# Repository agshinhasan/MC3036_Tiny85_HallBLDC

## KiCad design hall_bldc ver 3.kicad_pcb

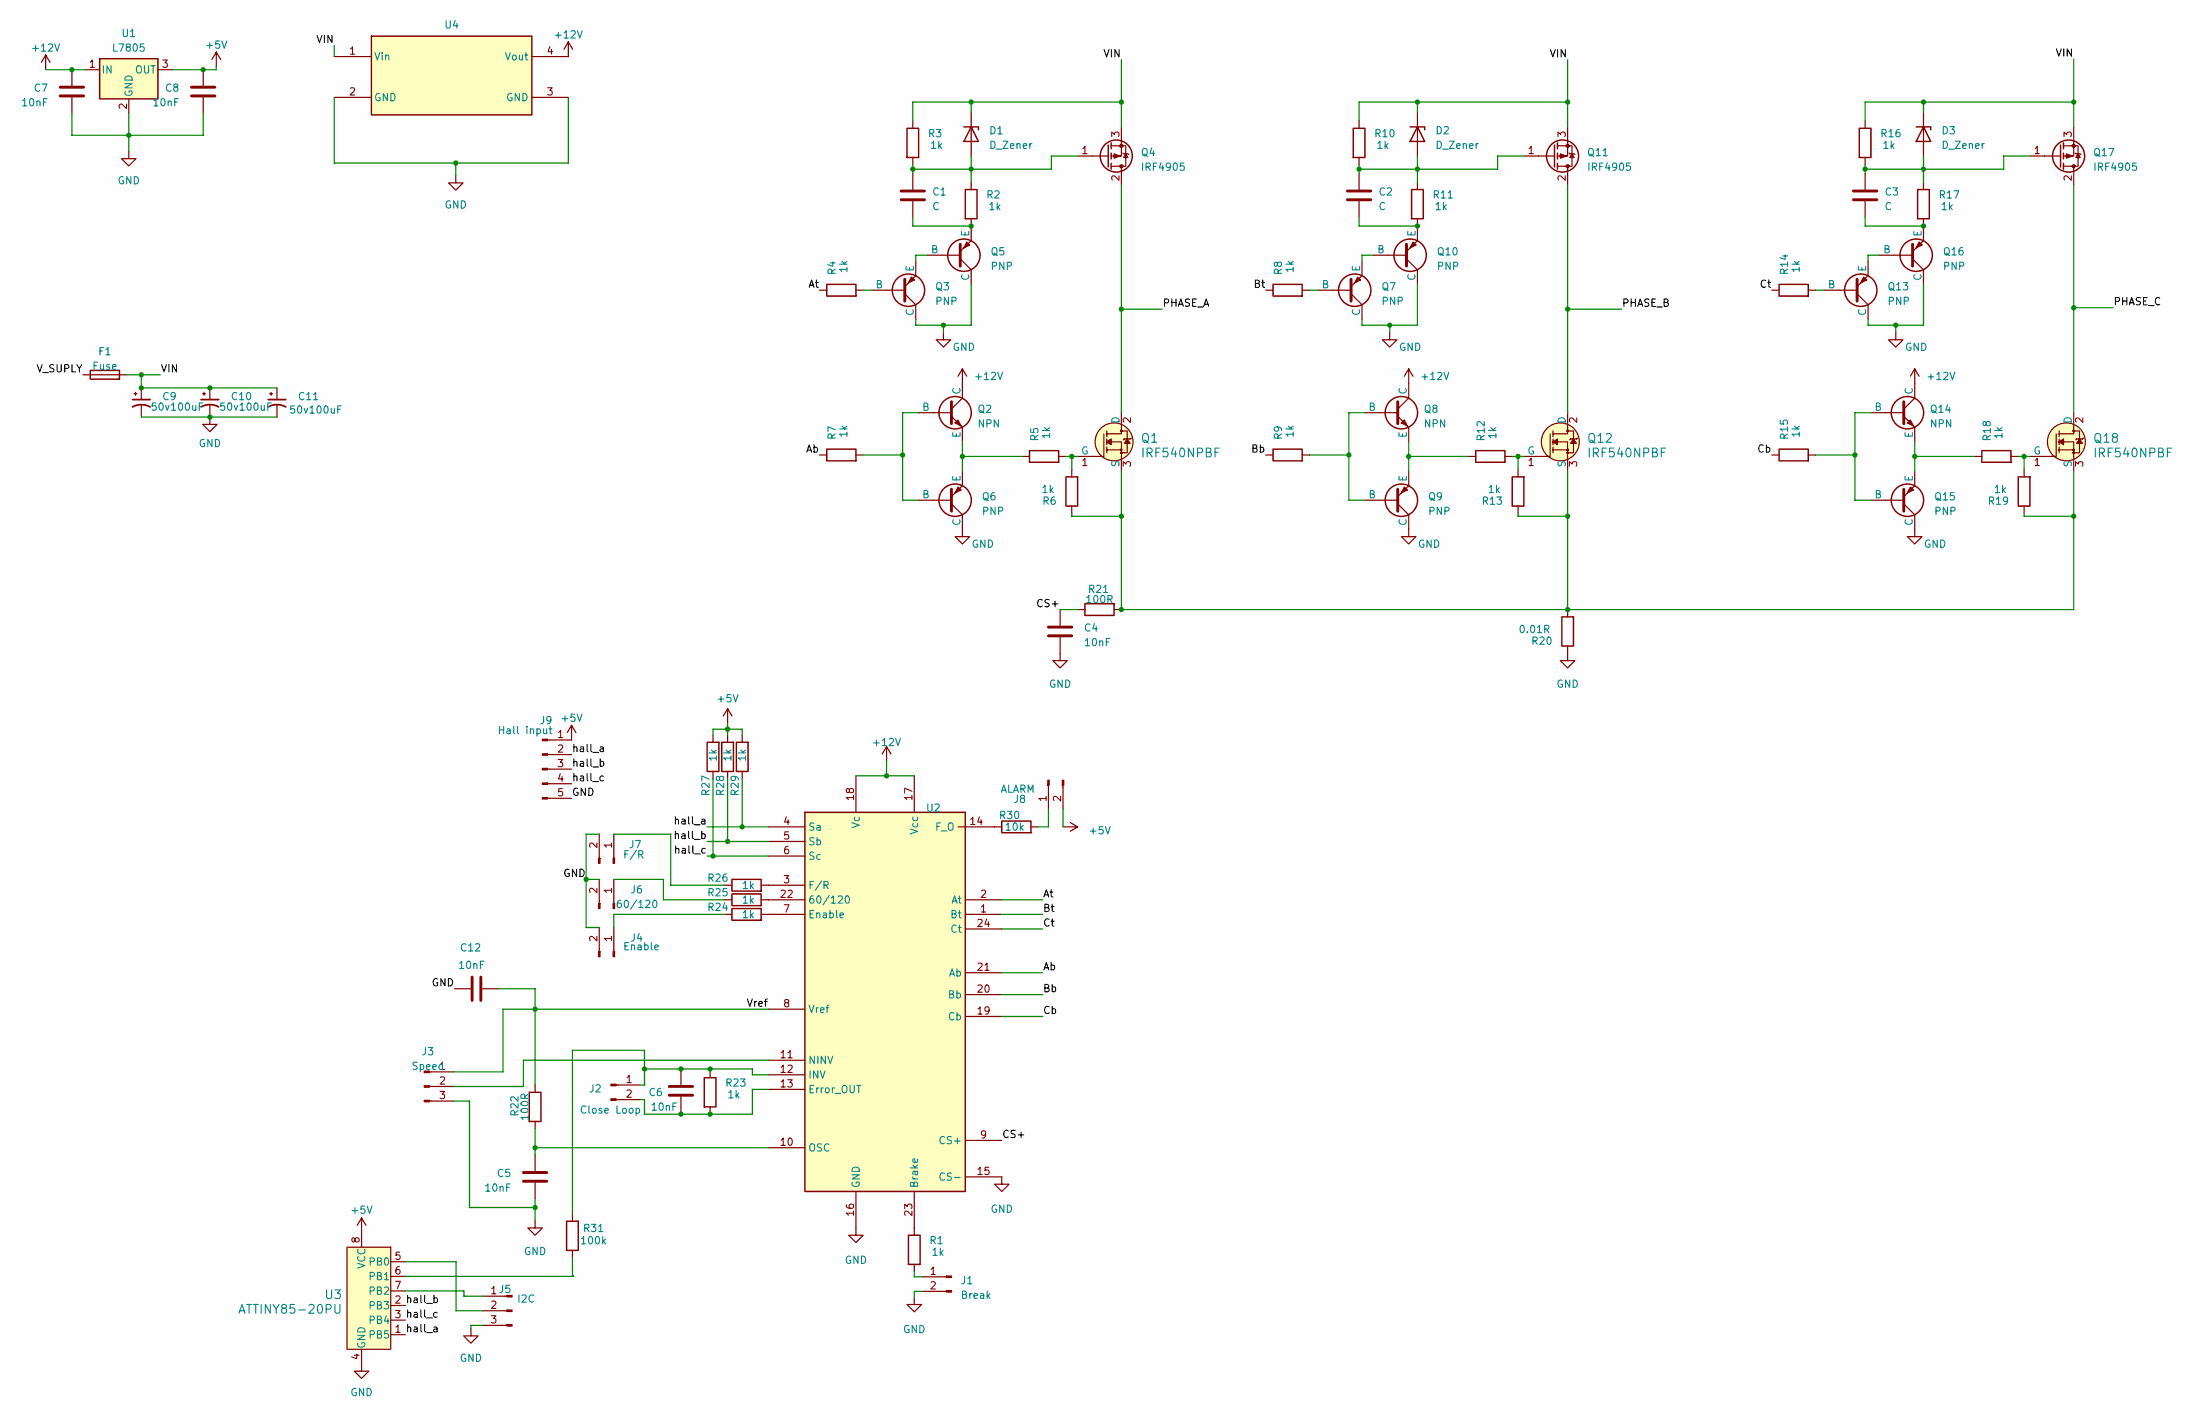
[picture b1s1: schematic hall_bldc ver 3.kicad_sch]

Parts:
C1, C2, C3: C; C_0805_2012Metric
C4, C5, C6, C12: 10nF; C_0805_2012Metric
C7, C8: 10nF; C_1206_3216Metric
C9, C10, C11: 50v100uF; CP_Radial_D10.0mm_P5.00mm
D1, D2, D3: D_Zener; D_A-405_P5.08mm_Vertical_AnodeUp
F1: Fuse; Fuseholder_Clip-5x20mm_Keystone_3512_Inline_P23.62x7.27mm_D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
J1: Break; PinHeader_1x02_P2.54mm_Vertical
J2: Close Loop; PinHeader_1x02_P2.54mm_Vertical
J3: Speed; PinHeader_1x03_P2.54mm_Vertical
J4: Enable; PinHeader_1x02_P2.54mm_Vertical
J5: I2C; PinHeader_1x03_P2.54mm_Vertical
J6: 60/120; PinHeader_1x02_P2.54mm_Vertical
J7: F/R; PinHeader_1x02_P2.54mm_Vertical
J8: ALARM; PinHeader_1x02_P2.54mm_Vertical
J9: Hall input; PinHeader_1x05_P2.54mm_Vertical
Q1, Q12, Q18: IRF540NPBF; TO-220-3; MPN IRF540NPBF; Digi-Key_PN IRF540NPBF-ND
Q2, Q8, Q14: NPN; SOT-23W
Q3, Q5, Q6, Q7, Q9, Q10, Q13, Q15, Q16: PNP; SOT-23W
Q4, Q11, Q17: IRF4905; TO-220-3_Vertical
R1, R4, R5, R6, R7, R8, R9, R12, R13, R14, R15, R18, R19, R23, R24, R25, R26, R27, R28, R29: 1k; R_0805_2012Metric
R2, R11, R17: 1k; R_Axial_DIN0207_L6.3mm_D2.5mm_P5.08mm_Vertical
R3, R10, R16: 1k; R_1206_3216Metric
R20: 0.01R; R_Axial_DIN0411_L9.9mm_D3.6mm_P15.24mm_Horizontal
R21, R22: 100R; R_0805_2012Metric
R30: 10k; R_0805_2012Metric
R31: 100k; R_0805_2012Metric
U1: L7805; TO-252-2
U2: DIP-24_W7.62mm_Socket_LongPads
U3: ATTINY85-20PU; DIP-8_W7.62mm; MPN ATTINY85-20PU; Digi-Key_PN ATTINY85-20PU-ND
U4: DC-DC

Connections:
+5V: C8.1, J8.2, J9.1, R27.2, R28.2, R29.2, U1.3 (OUT), U3.8 (VCC)
+12V: C7.1, Q2.3 (C), Q8.3 (C), Q14.3 (C), U1.1 (IN), U2.17 (Vcc), U2.18 (Vc), U4.4 (Vout)
/Ab: R7.1, U2.21 (Ab)
/At: R4.1, U2.2 (At)
/Bb: R9.1, U2.20 (Bb)
/Bt: R8.1, U2.1 (Bt)
/CS+: C4.1, R21.1, U2.9 (CS+)
/Cb: R15.1, U2.19 (Cb)
/Ct: R14.1, U2.24 (Ct)
/PHASE_A: Q1.2 (D), Q4.2 (D)
/PHASE_B: Q11.2 (D), Q12.2 (D)
/PHASE_C: Q17.2 (D), Q18.2 (D)
/VIN: C9.1, C10.1, C11.1, D1.1 (K), D2.1 (K), D3.1 (K), F1.2, Q4.3 (S), Q11.3 (S), Q17.3 (S), R3.1, R10.1, R16.1, U4.1 (Vin)
/V_SUPLY: F1.1
/Vref: C12.2, J3.1, R22.1, U2.8 (Vref)
/hall_a: J9.2, R29.1, U2.4 (Sa), U3.1 (PB5)
/hall_b: J9.3, R28.1, U2.5 (Sb), U3.2 (PB3)
/hall_c: J9.4, R27.1, U2.6 (Sc), U3.3 (PB4)
GND: C4.2, C5.2, C7.2, C8.2, C9.2, C10.2, C11.2, C12.1, J1.2, J3.3, J4.2, J5.3, J6.2, J7.2, J9.5, Q3.3 (C), Q5.3 (C), Q6.3 (C), Q7.3 (C), Q9.3 (C), Q10.3 (C), Q13.3 (C), Q15.3 (C), Q16.3 (C), R20.1, U1.2 (GND), U2.15 (CS-), U2.16 (GND), U3.4 (GND), U4.2 (GND), U4.3 (GND)
unnamed: C1.1, D1.2 (A), Q4.1 (G), R2.1, R3.2
unnamed: C2.1, D2.2 (A), Q11.1 (G), R10.2, R11.1
unnamed: C3.1, D3.2 (A), Q17.1 (G), R16.2, R17.1
unnamed: J1.1, R1.2
unnamed: C6.1, J2.1, R23.1, R31.2, U2.12 (INV)
unnamed: C6.2, J2.2, R23.2, U2.13 (Error_OUT)
unnamed: J3.2, U2.11 (NINV)
unnamed: J4.1, R24.1
unnamed: J5.1, U3.7 (PB2)
unnamed: J5.2, U3.5 (PB0)
unnamed: J6.1, R25.1
unnamed: J7.1, R26.1
unnamed: J8.1, R30.2
unnamed: Q1.1 (G), R5.2, R6.2
unnamed: Q1.3 (S), Q12.3 (S), Q18.3 (S), R6.1, R13.1, R19.1, R20.2, R21.2
unnamed: Q2.1 (B), Q6.1 (B), R7.2
unnamed: Q2.2 (E), Q6.2 (E), R5.1
unnamed: Q3.1 (B), R4.2
unnamed: Q3.2 (E), Q5.1 (B)
unnamed: C1.2, Q5.2 (E), R2.2
unnamed: Q7.1 (B), R8.2
unnamed: Q8.1 (B), Q9.1 (B), R9.2
unnamed: Q8.2 (E), Q9.2 (E), R12.1
unnamed: Q7.2 (E), Q10.1 (B)
unnamed: C2.2, Q10.2 (E), R11.2
unnamed: Q12.1 (G), R12.2, R13.2
unnamed: Q13.1 (B), R14.2
unnamed: Q13.2 (E), Q16.1 (B)
unnamed: Q14.1 (B), Q15.1 (B), R15.2
unnamed: Q14.2 (E), Q15.2 (E), R18.1
unnamed: C3.2, Q16.2 (E), R17.2
unnamed: Q18.1 (G), R18.2, R19.2
unnamed: R25.2, U2.22 (60/120)
unnamed: R1.1, U2.23 (Brake)
unnamed: R24.2, U2.7 (Enable)
unnamed: R30.1, U2.14 (F_O)
unnamed: R26.2, U2.3 (F/R)
unnamed: C5.1, R22.2, U2.10 (OSC)
unnamed: R31.1, U3.6 (PB1)

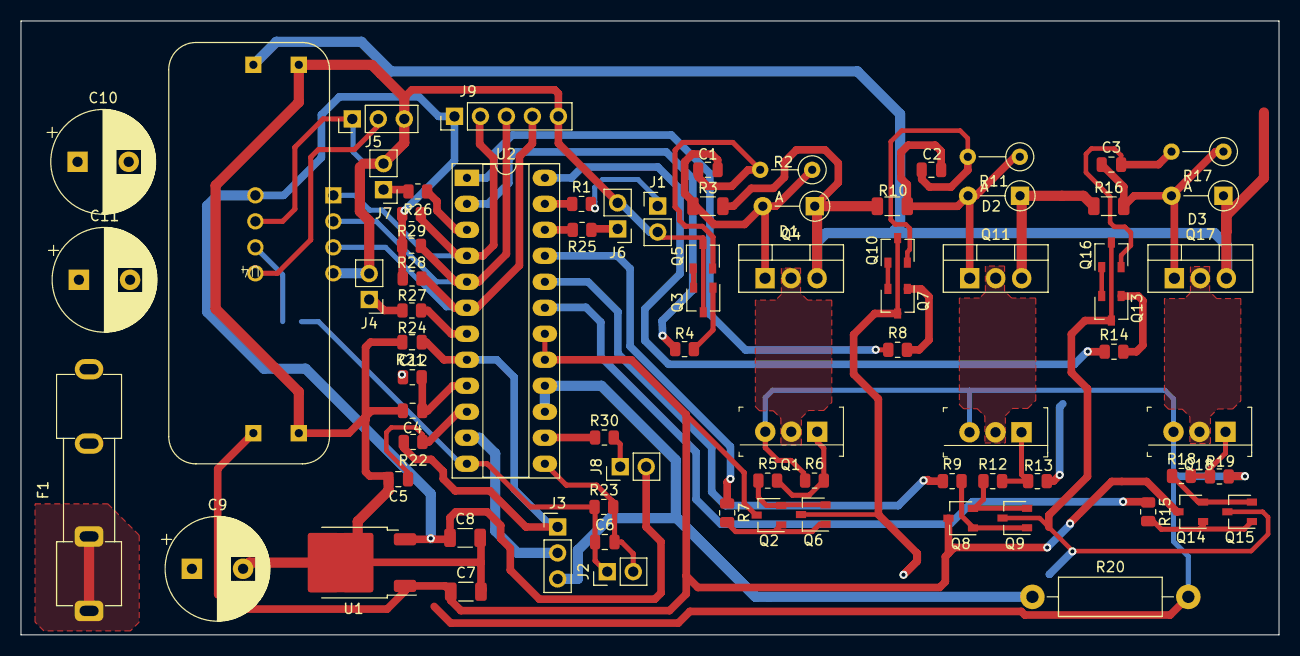
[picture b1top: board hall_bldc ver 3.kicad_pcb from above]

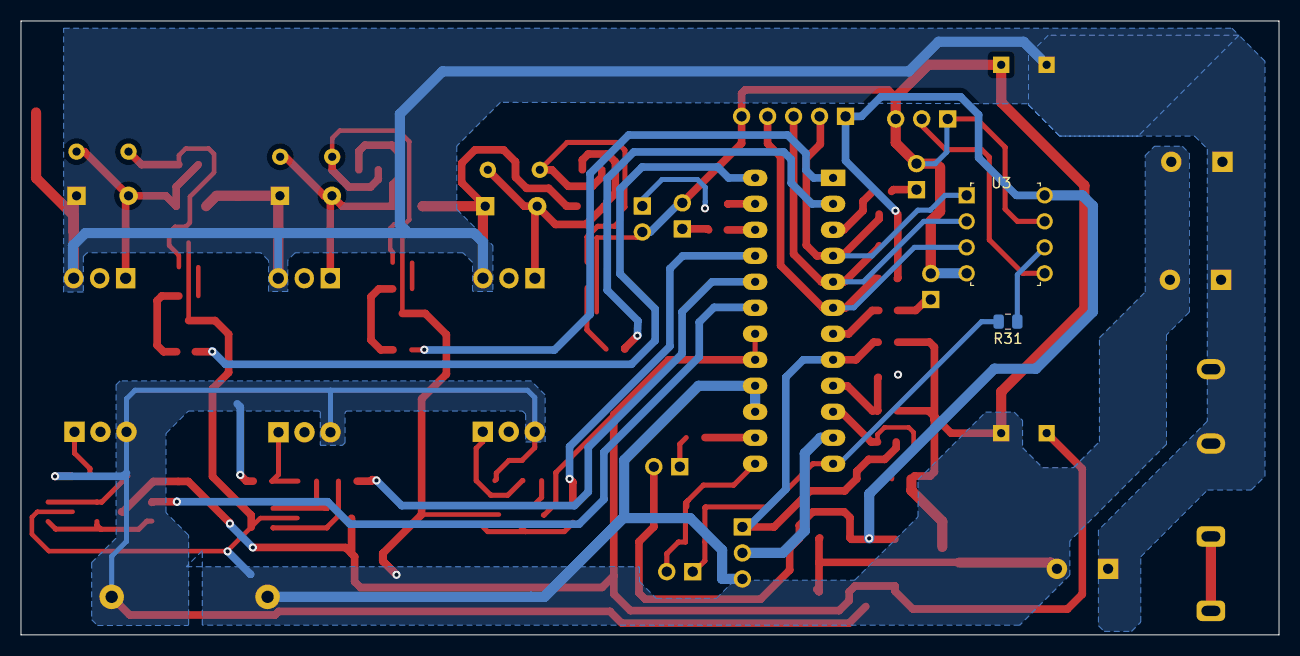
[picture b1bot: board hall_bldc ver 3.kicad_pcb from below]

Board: 2 copper layers, 123.0 x 60.0 mm, 78 parts (2 on the bottom side), 57 nets.
